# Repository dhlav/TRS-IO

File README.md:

# TRS-IO

TRS-IO gives a TRS-80 Model 1/III online capabilities and provides
access to a variety of services. TRS-IO currently features the
following capabilities:

1. Access to the <a href="https://retrostore.org">RetroStore</a>
2. <a href="http://frehd.com">FreHD</a> emulation
3. Access to files mounted on a SMB share or located on a micro-SD card
4. Access to remote servers via TCP
5. Virtual printer support

The TRS-IO versions for the Model 1 have some additional features that
are explained below. The following sections give an overview of TRS-IO as well as setup
instructions. This Github repository contains the complete source code
as well as the KiCad schematics for the PCB (Printed Circuit Board).
For the following descriptions it is assumed that an assembled TRS-IO
card is available.

### Overview

The figure below depicts the overall architecture. The TRS-80 machine
is connected to TRS-IO via the I/O Bus.  TRS-IO has a WiFi module that
connects to the local WiFi router. This allows TRS-IO to connect to
the Internet and access various services. Note that TRS-IO can only
connect to a 2.4 GHz WiFi network.

### Prerequisites

TRS-IO requires a TRS-80 Model III with 48kB of RAM or a Model 1 with 16kB of RAM.
Floppy disk drives or a cassette tape are not required.

### Feature list

TRS-IO support
TRS-IO comes in three different versions:

* TRS-IO for the Model III
* TRS-IO for the Model I using a builtin 32kB SRAM
* TRS-IO for the Model I using an FPGA

In the following, each of the versions is explained in detail.

### TRS-IO for the Model III

The following figure shows the top view of the TRS-IO card for the Model III:

1. Power supply via a micro-USB connector
2. Multi-color status LED
3. Status button
4. TRS-80 I/O bus connector
5. Micro-SD card reader
6. Disable FreHD jumper

The TRS-IO card needs to be connected to the TRS-80 Model III's I/O
Bus via a 50-pin ribbon cable (4). Furthermore, the TRS-IO card needs
a separate power supply via a standard 5V USB charger. The micro-USB
connector (1) plugs into the side of the TRS-IO card. The push button
(3) and the multi-color status LED (2) will be explained in the
configuration section.

### TRS-IO for the Model 1 (SRAM edition)

The following figure shows the top view of the TRS-IO card for the Model 1:

1. Power supply via a micro-USB connector
2. Multi-color status LED
3. Status button
4. TRS-80 I/O bus connector
5. Micro-SD card reader

The TRS-IO version for the Model 1 is almost identical to the Model III.
One difference is the I/O bus connector (4) is compatible with the 40-pin
expansion interface of the Model 1. There are several additional features
for the Model 1 version that are not relevant to the Model III version:

* A 32kB SRAM chip for a total of 48kB of total RAM.
* 25ms heartbeat timer to trigger the realtime clock.
* FreHD auto-boot for an unmodified M1.

### TRS-IO for the Model 1 (FPGA edition)

The TRS-IO project features a second version for the Model 1 that makes use
of an FGPA (Field Programmable Gate Array). Using an FPGA allows for some
advanced features not possible with the SRAM edition of TRS-IO. The following
figure shows the top view of the FPGA version for the Model 1:

1. Power supply via a micro-USB connector
2. Multi-color status LED
3. Status button
4. TRS-80 I/O bus connector
5. Micro-SD card reader
6. N/A
7. VGA connector
8. A15/VU configuration jumpers

This version of TRS-IO offers all the features of the SRAM edition of TRS-IO
as outlined in the previous section. Additionally, the FPGA edition also
offers a VGA connector (7) that can be used instead of a CRT monitor. This version
of TRS-IO also emlates the LE18 graphics cards. The color of the VGA signal can
be set to white (X=0), green (X=1), and amber (X=2) via the following OUT statements:

```OUT 31,0:OUT 31,5:OUT 31,X```

There are two configuation jumpers (8):
With the VU jumper, the ESP also powers the FPGA. When using this jumper, the FPGA
SHOULD NOT be powered via its own micro-USB connector; power should only be supplied
to the ESP's micro-USB connector (1). The A15 jumper regulates
the address range the FPGA responds to. Without the A15 jumper, the FPGA only
responds to memory read/write requests for the upper 32 kB (essentially mimicking the
upper RAM of the SRAM edition). With the A15 jumper, the FPGA will respond to the
complete 64kB address space of the Z80. This requires a modified Model 1 as the FPGA also
responds to ROM read requests.

### Configuring TRS-IO

The core of the TRS-IO card is an ESP32 microcontroller that features
a WiFi module that is used to connect to a WiFi router. After
physically connecting the TRS-IO card to a TRS-80 Model 1/III as
explained in the previous sections, the WiFi module on the ESP32
microcontroller first needs to be be configured with the credentials
of the local WiFi network.

While in setup mode, the TRS-IO's status LED will continuously blink
in white to indicate that it has not yet been configured. While in
that mode, TRS-IO will create an open access point called
"TRS-IO". Use a laptop to connect to this WiFi network and then use a
browser to visit URL <a
href="http://trs-io.local">trs-io.local</a>. The following web page
should appear in the browser:

Some hosts do not correctly handle mDNS that is used to resolve <a
href="http://trs-io.local">trs-io.local</a>. In that case, visit the
IP address <a href="http://192.168.4.1">192.168.4.1</a> instead.
The web interface shown above can be used to configure SSID and password of the WiFi
network that TRS-IO should connect to, the local timezone as well as
the credentials of a SMB share. For open networks leave the WiFi
password field empty. Note that TRS-IO cannot connect to WiFi networks
that use a capture portal. The timezone as well as the SMB share are
not required but will result in limited functionality.

Once all the information is provided, click on submit to upload the
parameters. TRS-IO will automatically reboot and try to connect to the
specified WiFi network. If successful, the LED will turn green for a
few seconds. If the credentials are wrong or if the specified WiFi
network is not accessible, the LED light will turn permanently red.

Note that TRS-IO will store all parameters in its local flash memory,
so the setup only needs to be performed once. Once TRS-IO is connected
to a WiFi router, it should still be possible to access URL <a
href="http://trs-io.local">trs-io.local</a> from a browser on the same
WiFi network. If mDNS is not supported by the host, the following BASIC
program can be used to determine TRS-IO's local IP address that was
assigned by the router:

```
10 OUT 236,16
20 OUT31,0:OUT31,4
30 C=INP(31):IF C=0 THEN END
40 PRINT CHR$(C);
50 GOTO 30
```

The web interface will also display two icons to indicate the status
of the SMB share and the micro-SD card (see screenshot above). Green
icons indicate that TRS-IO has access. Red icons indicate an error.
In that case, hovering the mouse over the red icon will display the
error message. It should be noted that TRS-IO needs to be rebooted
whenever a micro-SD card is inserted or ejected.

Pushing the status button will make the LED flash twice. The first time for
the WiFi status (green: WiFi connected; red: WiFi not connected) and a
second time for the SMB status (green: connected to SMB share; red:
not connected to SMB share). With proper configuration parameters, the
LED should flash green twice. Holding down the push button for more
than three seconds will erase all configuration parameters and place
TRS-IO back into setup mode (status LED flashing white). This
might be necessary if TRS-IO is moved to a different WiFi network.

The status LED indicates the state of TRS-IO:

* Blinking white: TRS-IO is not configured. It will create an open WiFi access point named "TRS-IO"
* Solid green: when TRS-IO has been configured with WiFi credentials and TRS-IO was able
  to connect to the WiFi network, the status LED will light in solid green for several seconds.
* Solid red: TRS-IO was configured with WiFi credentials but it was not possible to connect to the specified
  network. The reason could be wrong credentials or the specified network is itself offline. The push button can be
  used to reset TRS-IO into setup mode in case different credentials need to be provided.
* Solid blue: TRS-IO performs an OTA (Over-the-Air) update. TRS-IO will automatically detect
  newer firmware versions and will download and install the new firmware. The status LED will light solid blue during
  this process.
* Off: the status LED will be off during regular operations when TRS-IO is connected to the specified
  WiFi network and ready to accept commands from the TRS-80 Model III.
 
### FreHD

TRS-IO is compatible with the popular <a
href="http://frehd.com">FreHD</a> hard disk emulator. The FreHD disk
images can either be stored on a SMB share or on a micro-SD card.
If a micro-SD card is inserted, it will take precedence over
a mounted SMB share. Once TRS-IO is configured to access a SMB share,
simply copy the required files such as <a
href="http://members.iinet.net.au/~ianmav/trs80/downloads.htm">FREHD.ROM</a>
to the SMB share. Alternatively, the disk images can be transferred
to the micro-SD card. The IMPORT/EXPORT utilities will access files on the
SMB share or micro-SD card respectively.

### Virtual Printer Interface

TRS-IO support a virtual printer interface. Visiting <a
href="http://trs-io.local/printer">trs-io.local/printer</a> from a browser
will open the printer interface. Any printer output from the M1/MIII will
be displayed in the printer interface. If the host cannot resolve the mDNS name
trs-io.local, the above BASIC program can be used to determine the TRS-80's
IP address.

 ### Launching the native RetroStore Client

The <a href="https://retrostore.org">RetroStore</a> hosts applications
for the Tandy Radio Shack vintage computers and allows to seamlessly
download and run these applications without the need of cassettes or
floppy disks. TRS-IO acts as a gateway to the <a
href="https://retrostore.org">RetroStore</a>. This requires to run a
program on the TRS-80 that interfaces with TRS-IO. This program is
available as a regular <a
href="https://github.com/apuder/TRS-IO/blob/master/src/esp/components/retrostore/rsclient.cmd">CMD</a>
executable.  For TRS-80 machines with attached physical floppy disks,
this CMD executable can be copied to a floppy disk and launched the
usual way. For TRS-80 machines that have neither floppy disk drives
nor cassette drives, it is also possible to bootstrap the native
client via the following short BASIC program:
 
 ```BASIC
 10 OUT236,16
 20 OUT31,3
 30 OUT31,1
 40 N=INP(31)+256*INP(31)
 50 FOR X=1 TO N:POKE20735+X,INP(31):NEXT
 RUN
 SYSTEM
 *? /20736
 ```
 
The above BASIC program will download the CMD executable from TRS-IO
and launch the native client.  Note that this procedure needs to be
repeated every time the TRS-80 is turned on.
 
### Using the native RetroStore Client

After successfully launching the native RetroStore client, the monitor
of the TRS-80 should look like this:

The screenshot above shows the main menu of the native RetroStore
client. The arrow indicates the currently selected menu item.  The up
and down cursor keys can be used to move between the various menu
items. Hitting the ENTER key will activate the currently selected
menu item. Pressing CLEAR or BREAK in sub-menus will return to the
previous menu.
 
Keyboard controls:
 
 * Cursor up/down: toggle menu selection
 * ENTER: select current menu selection
 * BREAK/CLEAR: exit to previous screen

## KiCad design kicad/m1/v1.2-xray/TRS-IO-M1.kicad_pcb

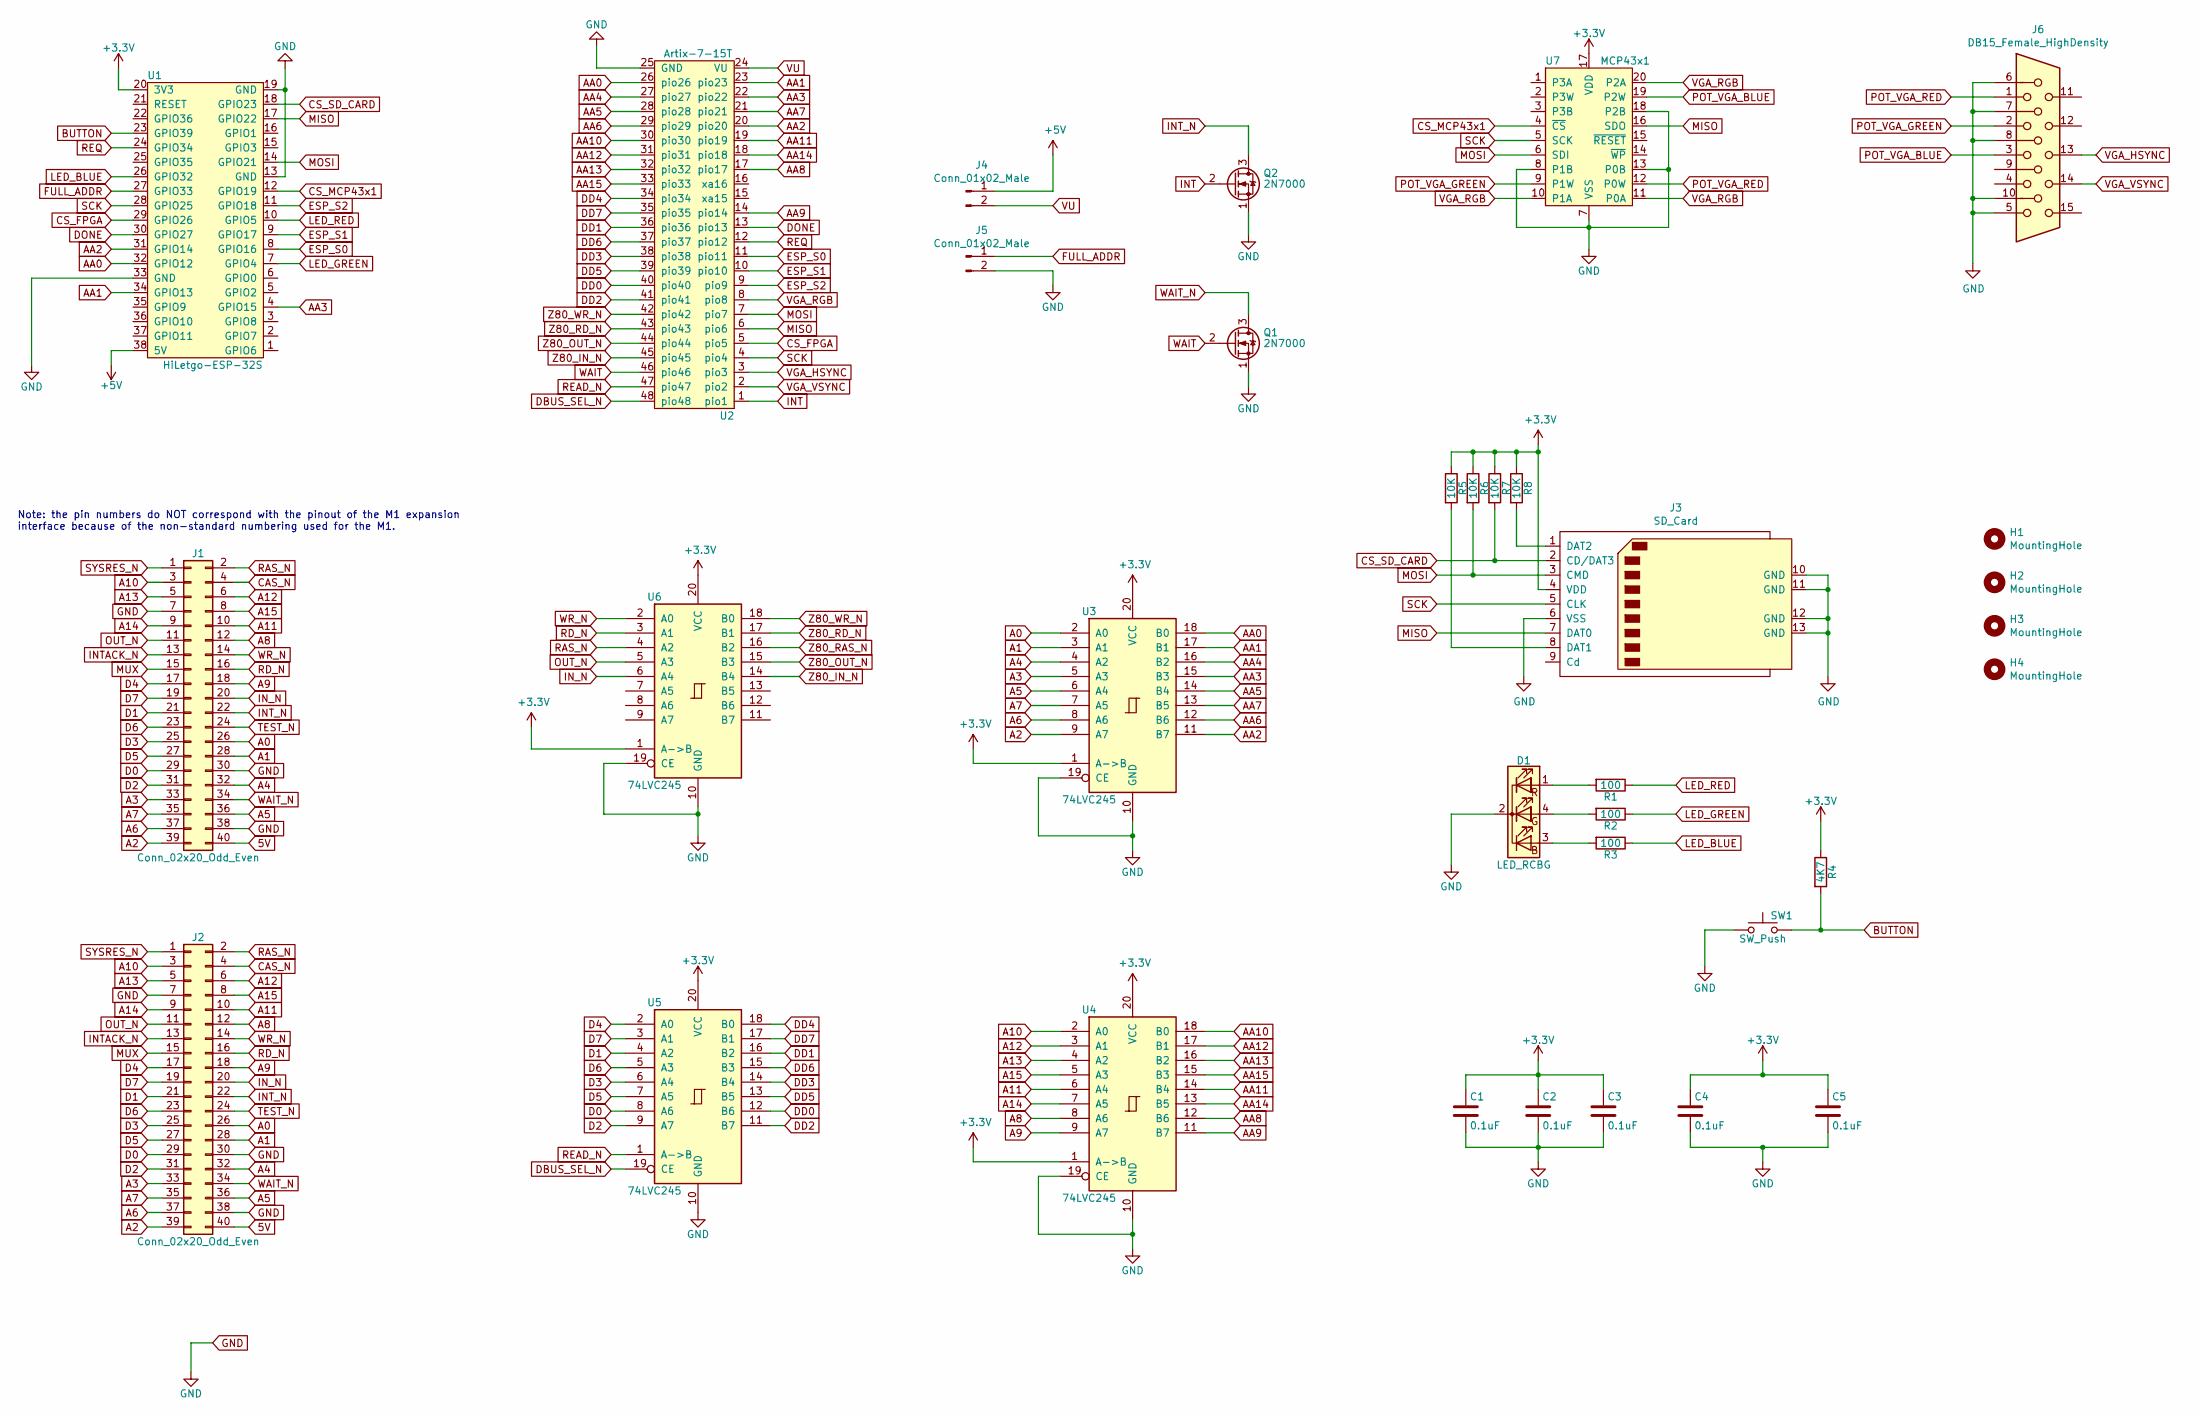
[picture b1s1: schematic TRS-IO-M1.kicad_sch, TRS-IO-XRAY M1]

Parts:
C1, C2, C3, C4, C5: 0.1uF; C_Disc_D3.0mm_W2.0mm_P2.50mm
D1: LED_RCBG; LED_D5.0mm-4_RGB
H1, H2, H3, H4: MountingHole; MountingHole_3mm_Pad_Via
J1: Conn_02x20_Odd_Even; PinHeader_2x20_P2.54mm_Vertical
J2: Conn_02x20_Odd_Even; TRSEDGE
J3: SD_Card; TFP09-2-12B
J4, J5: Conn_01x02_Male; PinHeader_1x02_P2.54mm_Vertical
J6: DB15_Female_HighDensity; DB_15F-VGA
Q1, Q2: 2N7000; TO-92_Inline
R1, R2, R3: 100; R_Axial_DIN0207_L6.3mm_D2.5mm_P7.62mm_Horizontal
R4: 4K7; R_Axial_DIN0207_L6.3mm_D2.5mm_P7.62mm_Horizontal
R5, R6, R7, R8: 10K; R_Axial_DIN0207_L6.3mm_D2.5mm_P7.62mm_Horizontal
SW1: SW_Push; SW_PUSH_6mm_H9.5mm
U1: HiLetgo-ESP-32S; DIP-38_W22.9mm
U2: Artix-7-15T; DIP-48_600_ELL
U3, U4, U5, U6: 74LVC245; DIP-20_W7.62mm
U7: MCP43x1; TSSOP-20_4.4x6.5mm_P0.65mm

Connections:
5V: J1.40, J2.40
+3V3: C1.1, C2.1, C3.1, C4.1, C5.1, J3.4 (VDD), R4.1, R5.1, R6.1, R7.1, R8.1, U1.20 (3V3), U3.1 (A->B), U3.20 (VCC), U4.1 (A->B), U4.20 (VCC), U5.20 (VCC), U6.1 (A->B), U6.20 (VCC), U7.17 (VDD)
+5V: J4.1, U1.38 (5V)
A0: J1.26, J2.26, U3.2 (A0)
A1: J1.28, J2.28, U3.3 (A1)
A2: J1.39, J2.39, U3.9 (A7)
A3: J1.33, J2.33, U3.5 (A3)
A4: J1.32, J2.32, U3.4 (A2)
A5: J1.36, J2.36, U3.6 (A4)
A6: J1.37, J2.37, U3.8 (A6)
A7: J1.35, J2.35, U3.7 (A5)
A8: J1.12, J2.12, U4.8 (A6)
A9: J1.18, J2.18, U4.9 (A7)
A10: J1.3, J2.3, U4.2 (A0)
A11: J1.10, J2.10, U4.6 (A4)
A12: J1.6, J2.6, U4.3 (A1)
A13: J1.5, J2.5, U4.4 (A2)
A14: J1.9, J2.9, U4.7 (A5)
A15: J1.8, J2.8, U4.5 (A3)
AA0: U1.32 (GPIO12), U2.26 (pio26), U3.18 (B0)
AA1: U1.34 (GPIO13), U2.23 (pio23), U3.17 (B1)
AA2: U1.31 (GPIO14), U2.20 (pio20), U3.11 (B7)
AA3: U1.4 (GPIO15), U2.22 (pio22), U3.15 (B3)
AA4: U2.27 (pio27), U3.16 (B2)
AA5: U2.28 (pio28), U3.14 (B4)
AA6: U2.29 (pio29), U3.12 (B6)
AA7: U2.21 (pio21), U3.13 (B5)
AA8: U2.17 (pio17), U4.12 (B6)
AA9: U2.14 (pio14), U4.11 (B7)
AA10: U2.30 (pio30), U4.18 (B0)
AA11: U2.19 (pio19), U4.14 (B4)
AA12: U2.31 (pio31), U4.17 (B1)
AA13: U2.32 (pio32), U4.16 (B2)
AA14: U2.18 (pio18), U4.13 (B5)
AA15: U2.33 (pio33), U4.15 (B3)
BUTTON: R4.2, SW1.2, U1.23 (GPIO39)
CAS_N: J1.4, J2.4
CS_FPGA: U1.29 (GPIO26), U2.5 (pio5)
CS_MCP43x1: U1.12 (GPIO19), U7.4 (~CS)
CS_SD_CARD: J3.2 (CD/DAT3), R7.2, U1.18 (GPIO23)
D0: J1.29, J2.29, U5.8 (A6)
D1: J1.21, J2.21, U5.4 (A2)
D2: J1.31, J2.31, U5.9 (A7)
D3: J1.25, J2.25, U5.6 (A4)
D4: J1.17, J2.17, U5.2 (A0)
D5: J1.27, J2.27, U5.7 (A5)
D6: J1.23, J2.23, U5.5 (A3)
D7: J1.19, J2.19, U5.3 (A1)
DBUS_SEL_N: U2.48 (pio48), U5.19 (CE)
DD0: U2.40 (pio40), U5.12 (B6)
DD1: U2.36 (pio36), U5.16 (B2)
DD2: U2.41 (pio41), U5.11 (B7)
DD3: U2.38 (pio38), U5.14 (B4)
DD4: U2.34 (pio34), U5.18 (B0)
DD5: U2.39 (pio39), U5.13 (B5)
DD6: U2.37 (pio37), U5.15 (B3)
DD7: U2.35 (pio35), U5.17 (B1)
DONE: U1.30 (GPIO27), U2.13 (pio13)
ESP_S0: U1.8 (GPIO16), U2.11 (pio11)
ESP_S1: U1.9 (GPIO17), U2.10 (pio10)
ESP_S2: U1.11 (GPIO18), U2.9 (pio9)
FULL_ADDR: J5.1, U1.27 (GPIO33)
GND: C1.2, C2.2, C3.2, C4.2, C5.2, D1.2 (K), J1.7, J1.30, J1.38, J2.7, J2.30, J2.38, J3.6 (VSS), J3.10 (GND), J3.11 (GND), J3.12 (GND), J3.13 (GND), J5.2, J6.5, J6.6, J6.7, J6.8, J6.10, Q1.1 (S), Q2.1 (S), SW1.1, U1.13 (GND), U1.19 (GND), U1.33 (GND), U2.25 (GND), U3.10 (GND), U3.19 (CE), U4.10 (GND), U4.19 (CE), U5.10 (GND), U6.10 (GND), U6.19 (CE), U7.7 (VSS), U7.8 (P1B), U7.13 (P0B), U7.18 (P2B)
INT: Q2.2 (G), U2.1 (pio1)
INTACK_N: J1.13, J2.13
INT_N: J1.22, J2.22, Q2.3 (D)
IN_N: J1.20, J2.20, U6.6 (A4)
LED_BLUE: R3.1, U1.26 (GPIO32)
LED_GREEN: R2.1, U1.7 (GPIO4)
LED_RED: R1.1, U1.10 (GPIO5)
MISO: J3.7 (DAT0), U1.17 (GPIO22), U2.6 (pio6), U7.16 (SDO)
MOSI: J3.3 (CMD), R6.2, U1.14 (GPIO21), U2.7 (pio7), U7.6 (SDI)
MUX: J1.15, J2.15
unnamed: D1.1 (RA), R1.2
unnamed: D1.3 (BA), R3.2
unnamed: D1.4 (GA), R2.2
unnamed: J3.1 (DAT2), R8.2
unnamed: J3.8 (DAT1), R5.2
OUT_N: J1.11, J2.11, U6.5 (A3)
POT_VGA_BLUE: J6.3, U7.19 (P2W)
POT_VGA_GREEN: J6.2, U7.9 (P1W)
POT_VGA_RED: J6.1, U7.12 (P0W)
RAS_N: J1.2, J2.2, U6.4 (A2)
RD_N: J1.16, J2.16, U6.3 (A1)
READ_N: U2.47 (pio47), U5.1 (A->B)
REQ: U1.24 (GPIO34), U2.12 (pio12)
SCK: J3.5 (CLK), U1.28 (GPIO25), U2.4 (pio4), U7.5 (SCK)
SYSRES_N: J1.1, J2.1
TEST_N: J1.24, J2.24
VGA_HSYNC: J6.13, U2.3 (pio3)
VGA_RGB: U2.8 (pio8), U7.10 (P1A), U7.11 (P0A), U7.20 (P2A)
VGA_VSYNC: J6.14, U2.2 (pio2)
VU: J4.2, U2.24 (VU)
WAIT: Q1.2 (G), U2.46 (pio46)
WAIT_N: J1.34, J2.34, Q1.3 (D)
WR_N: J1.14, J2.14, U6.2 (A0)
Z80_IN_N: U2.45 (pio45), U6.14 (B4)
Z80_OUT_N: U2.44 (pio44), U6.15 (B3)
Z80_RAS_N: U6.16 (B2)
Z80_RD_N: U2.43 (pio43), U6.17 (B1)
Z80_WR_N: U2.42 (pio42), U6.18 (B0)

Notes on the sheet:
Note: the pin numbers do NOT correspond with the pinout of the M1 expansion interface because of the non-standard numbering used for the M1.

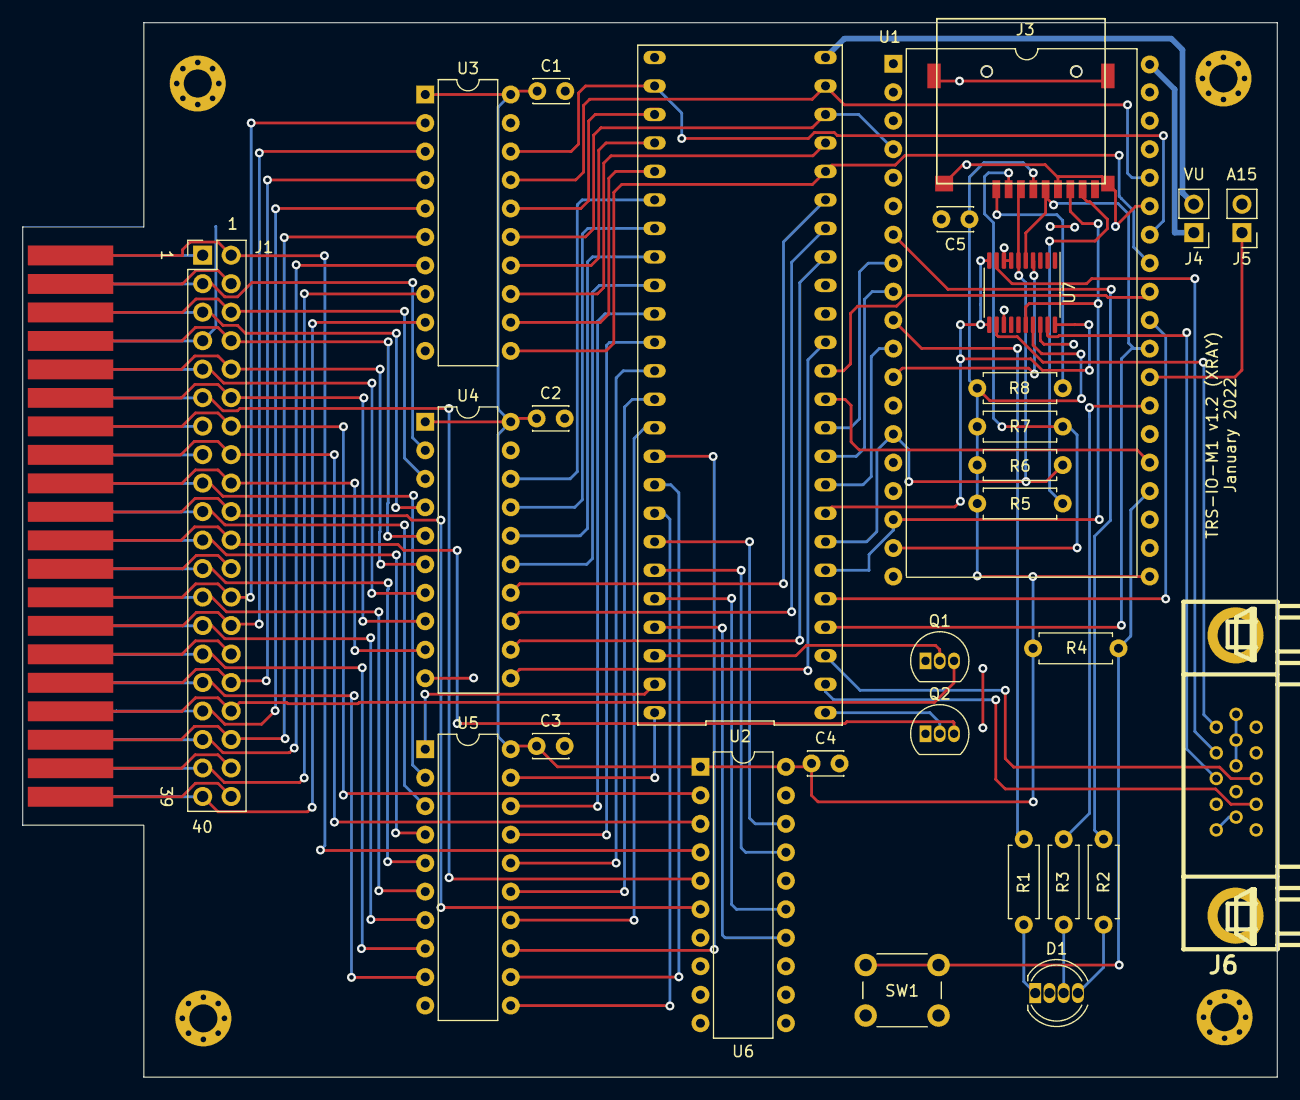
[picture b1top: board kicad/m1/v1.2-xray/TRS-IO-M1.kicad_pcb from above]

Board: 2 copper layers, 111.9 x 94.0 mm, 34 parts (0 on the bottom side), 100 nets.

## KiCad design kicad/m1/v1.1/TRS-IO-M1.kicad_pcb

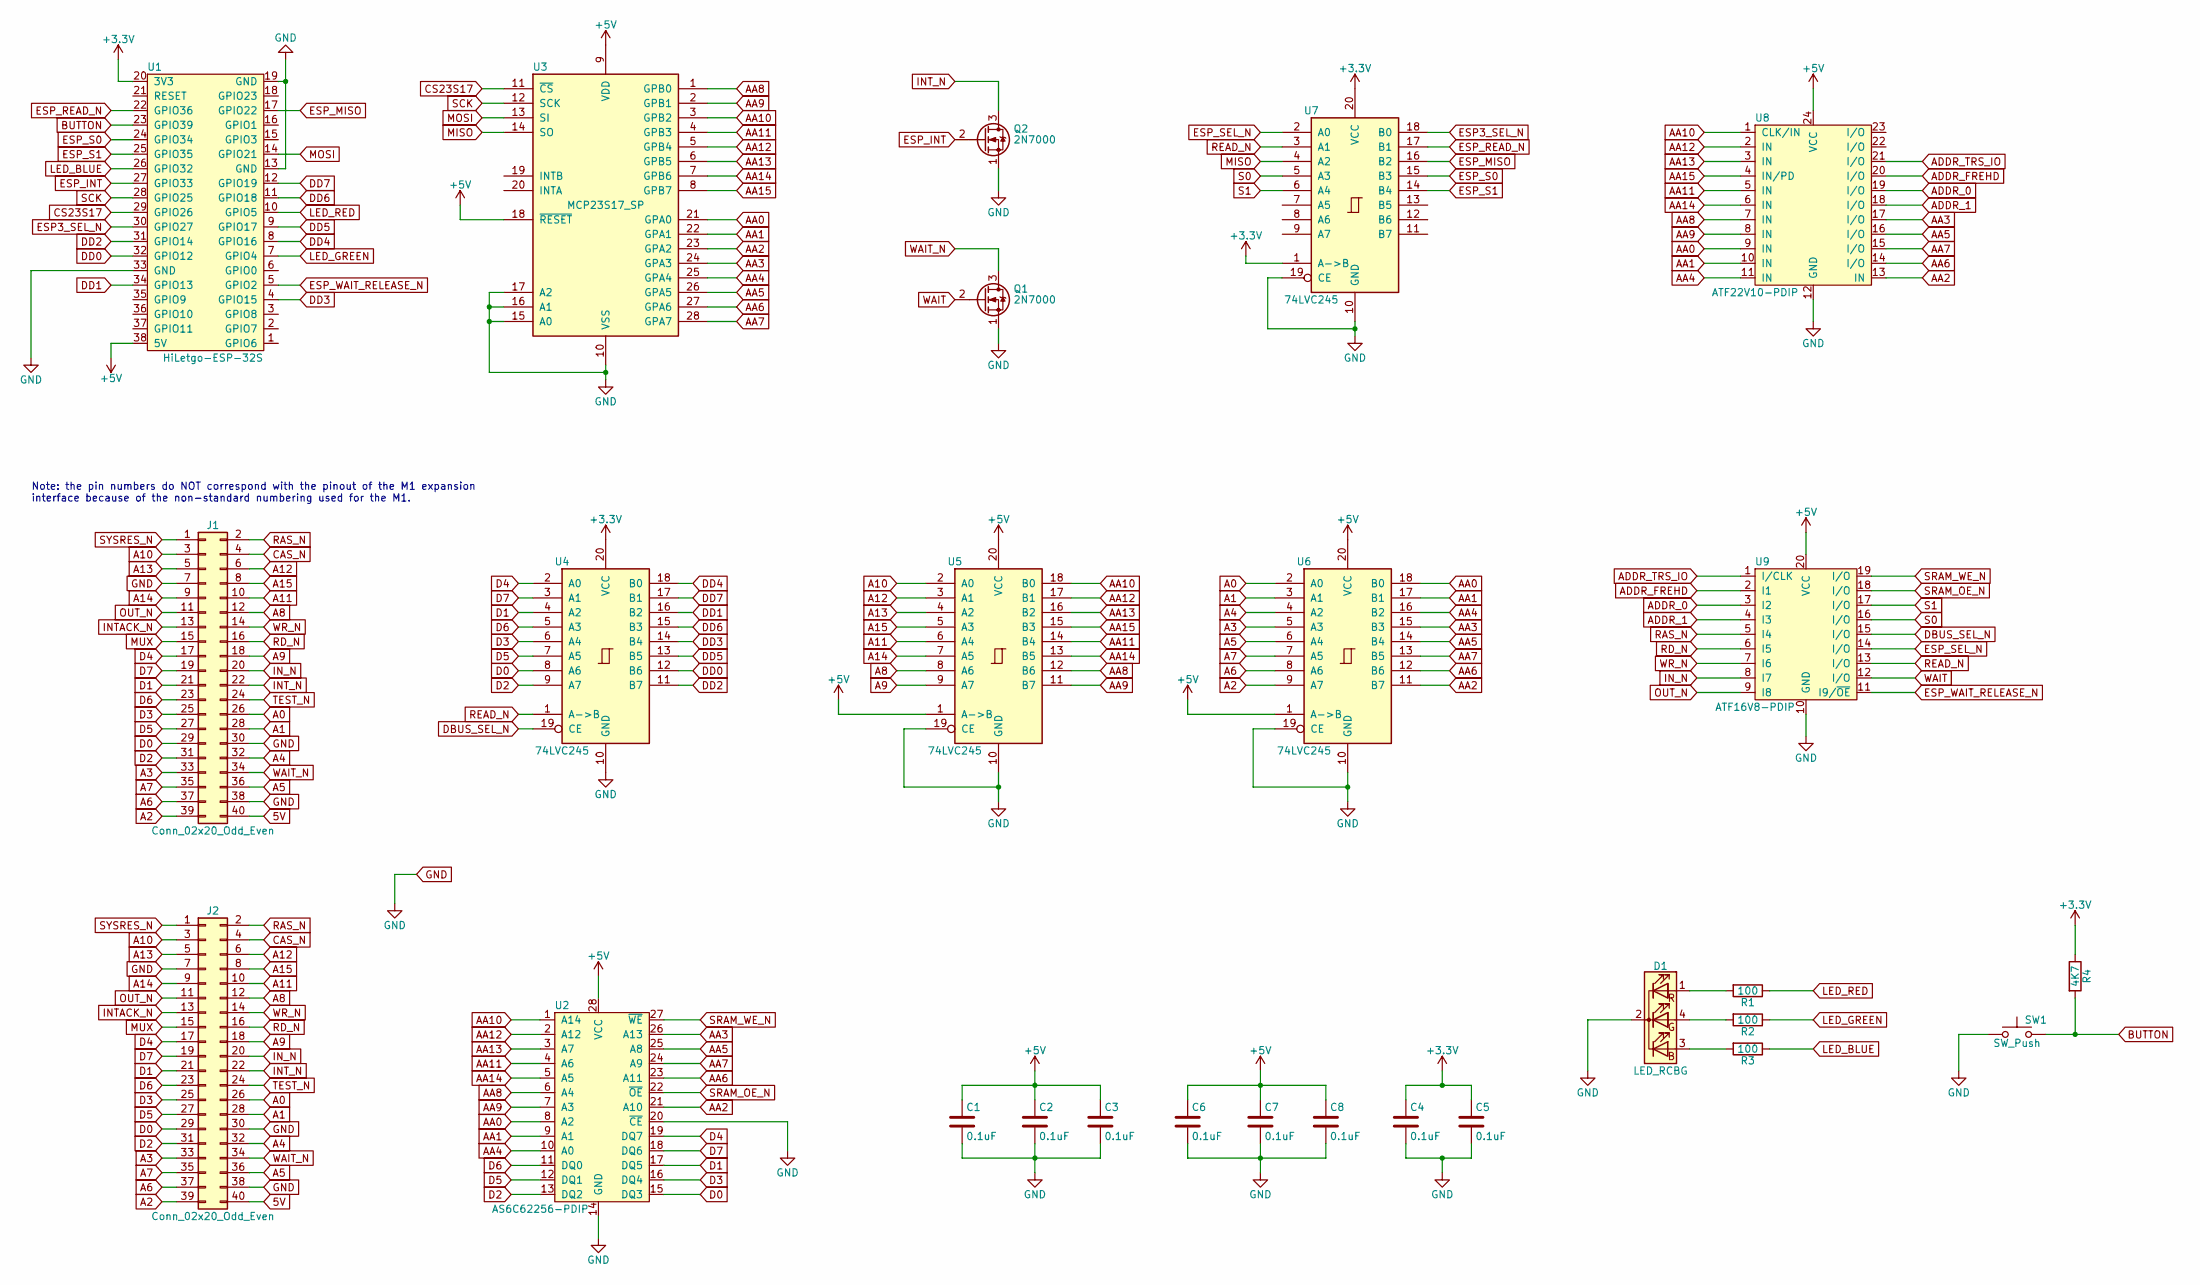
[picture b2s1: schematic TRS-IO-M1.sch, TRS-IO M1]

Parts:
C1, C2, C3, C4, C5, C6, C7, C8: 0.1uF; C_Disc_D3.0mm_W2.0mm_P2.50mm
D1: LED_RCBG; LED_D5.0mm-4_RGB
J1: Conn_02x20_Odd_Even; PinHeader_2x20_P2.54mm_Vertical
J2: Conn_02x20_Odd_Even; TRSEDGE
Q1, Q2: 2N7000; TO-92_Inline
R1, R2, R3: 100; R_Axial_DIN0207_L6.3mm_D2.5mm_P7.62mm_Horizontal
R4: 4K7; R_Axial_DIN0207_L6.3mm_D2.5mm_P7.62mm_Horizontal
SW1: SW_Push; SW_PUSH_6mm_H9.5mm
U1: HiLetgo-ESP-32S; DIP-38_W22.9mm
U2: AS6C62256-PDIP; DIP-28_W15.24mm
U3: MCP23S17_SP; DIP-28_W7.62mm
U4, U5, U6, U7: 74LVC245; DIP-20_W7.62mm
U8: ATF22V10-PDIP; DIP-24_W7.62mm
U9: ATF16V8-PDIP; DIP-20_W7.62mm

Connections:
5V: J1.40, J2.40
+3V3: C4.1, C5.1, R4.1, U1.20 (3V3), U4.20 (VCC), U7.1 (A->B), U7.20 (VCC)
+5V: C1.1, C2.1, C3.1, C6.1, C7.1, C8.1, U1.38 (5V), U2.28 (VCC), U3.9 (VDD), U3.18 (~RESET~), U5.1 (A->B), U5.20 (VCC), U6.1 (A->B), U6.20 (VCC), U8.24 (VCC), U9.20 (VCC)
A0: J1.26, J2.26, U6.2 (A0)
A1: J1.28, J2.28, U6.3 (A1)
A2: J1.39, J2.39, U6.9 (A7)
A3: J1.33, J2.33, U6.5 (A3)
A4: J1.32, J2.32, U6.4 (A2)
A5: J1.36, J2.36, U6.6 (A4)
A6: J1.37, J2.37, U6.8 (A6)
A7: J1.35, J2.35, U6.7 (A5)
A8: J1.12, J2.12, U5.8 (A6)
A9: J1.18, J2.18, U5.9 (A7)
A10: J1.3, J2.3, U5.2 (A0)
A11: J1.10, J2.10, U5.6 (A4)
A12: J1.6, J2.6, U5.3 (A1)
A13: J1.5, J2.5, U5.4 (A2)
A14: J1.9, J2.9, U5.7 (A5)
A15: J1.8, J2.8, U5.5 (A3)
AA0: U2.8 (A2), U3.21 (GPA0), U6.18 (B0), U8.9 (IN)
AA1: U2.9 (A1), U3.22 (GPA1), U6.17 (B1), U8.10 (IN)
AA2: U2.21 (A10), U3.23 (GPA2), U6.11 (B7), U8.13 (IN)
AA3: U2.26 (A13), U3.24 (GPA3), U6.15 (B3), U8.17 (I/O)
AA4: U2.10 (A0), U3.25 (GPA4), U6.16 (B2), U8.11 (IN)
AA5: U2.25 (A8), U3.26 (GPA5), U6.14 (B4), U8.16 (I/O)
AA6: U2.23 (A11), U3.27 (GPA6), U6.12 (B6), U8.14 (I/O)
AA7: U2.24 (A9), U3.28 (GPA7), U6.13 (B5), U8.15 (I/O)
AA8: U2.6 (A4), U3.1 (GPB0), U5.12 (B6), U8.7 (IN)
AA9: U2.7 (A3), U3.2 (GPB1), U5.11 (B7), U8.8 (IN)
AA10: U2.1 (A14), U3.3 (GPB2), U5.18 (B0), U8.1 (CLK/IN)
AA11: U2.4 (A6), U3.4 (GPB3), U5.14 (B4), U8.5 (IN)
AA12: U2.2 (A12), U3.5 (GPB4), U5.17 (B1), U8.2 (IN)
AA13: U2.3 (A7), U3.6 (GPB5), U5.16 (B2), U8.3 (IN)
AA14: U2.5 (A5), U3.7 (GPB6), U5.13 (B5), U8.6 (IN)
AA15: U3.8 (GPB7), U5.15 (B3), U8.4 (IN/PD)
ADDR_0: U8.19 (I/O), U9.3 (I2)
ADDR_1: U8.18 (I/O), U9.4 (I3)
ADDR_FREHD: U8.20 (I/O), U9.2 (I1)
ADDR_TRS_IO: U8.21 (I/O), U9.1 (I/CLK)
BUTTON: R4.2, SW1.2, U1.23 (GPIO39)
CAS_N: J1.4, J2.4
CS23S17: U1.29 (GPIO26), U3.11 (~CS~)
D0: J1.29, J2.29, U2.15 (DQ3), U4.8 (A6)
D1: J1.21, J2.21, U2.17 (DQ5), U4.4 (A2)
D2: J1.31, J2.31, U2.13 (DQ2), U4.9 (A7)
D3: J1.25, J2.25, U2.16 (DQ4), U4.6 (A4)
D4: J1.17, J2.17, U2.19 (DQ7), U4.2 (A0)
D5: J1.27, J2.27, U2.12 (DQ1), U4.7 (A5)
D6: J1.23, J2.23, U2.11 (DQ0), U4.5 (A3)
D7: J1.19, J2.19, U2.18 (DQ6), U4.3 (A1)
DBUS_SEL_N: U4.19 (CE), U9.15 (I/O)
DD0: U1.32 (GPIO12), U4.12 (B6)
DD1: U1.34 (GPIO13), U4.16 (B2)
DD2: U1.31 (GPIO14), U4.11 (B7)
DD3: U1.4 (GPIO15), U4.14 (B4)
DD4: U1.8 (GPIO16), U4.18 (B0)
DD5: U1.9 (GPIO17), U4.13 (B5)
DD6: U1.11 (GPIO18), U4.15 (B3)
DD7: U1.12 (GPIO19), U4.17 (B1)
ESP3_SEL_N: U1.30 (GPIO27), U7.18 (B0)
ESP_INT: Q2.2 (G), U1.27 (GPIO33)
ESP_MISO: U1.17 (GPIO22), U7.16 (B2)
ESP_READ_N: U1.22 (GPIO36), U7.17 (B1)
ESP_S0: U1.24 (GPIO34), U7.15 (B3)
ESP_S1: U1.25 (GPIO35), U7.14 (B4)
ESP_SEL_N: U7.2 (A0), U9.14 (I/O)
ESP_WAIT_RELEASE_N: U1.5 (GPIO2), U9.11 (I9/~OE)
GND: C1.2, C2.2, C3.2, C4.2, C5.2, C6.2, C7.2, C8.2, D1.2 (K), J1.7, J1.30, J1.38, J2.7, J2.30, J2.38, Q1.1 (S), Q2.1 (S), SW1.1, U1.13 (GND), U1.19 (GND), U1.33 (GND), U2.14 (GND), U2.20 (~CE), U3.10 (VSS), U3.15 (A0), U3.16 (A1), U3.17 (A2), U4.10 (GND), U5.10 (GND), U5.19 (CE), U6.10 (GND), U6.19 (CE), U7.10 (GND), U7.19 (CE), U8.12 (GND), U9.10 (GND)
INTACK_N: J1.13, J2.13
INT_N: J1.22, J2.22, Q2.3 (D)
IN_N: J1.20, J2.20, U9.8 (I7)
LED_BLUE: R3.1, U1.26 (GPIO32)
LED_GREEN: R2.1, U1.7 (GPIO4)
LED_RED: R1.1, U1.10 (GPIO5)
MISO: U3.14 (SO), U7.4 (A2)
MOSI: U1.14 (GPIO21), U3.13 (SI)
MUX: J1.15, J2.15
unnamed: D1.1 (RA), R1.2
unnamed: D1.3 (BA), R3.2
unnamed: D1.4 (GA), R2.2
OUT_N: J1.11, J2.11, U9.9 (I8)
RAS_N: J1.2, J2.2, U9.5 (I4)
RD_N: J1.16, J2.16, U9.6 (I5)
READ_N: U4.1 (A->B), U7.3 (A1), U9.13 (I/O)
S0: U7.5 (A3), U9.16 (I/O)
S1: U7.6 (A4), U9.17 (I/O)
SCK: U1.28 (GPIO25), U3.12 (SCK)
SRAM_OE_N: U2.22 (~OE), U9.18 (I/O)
SRAM_WE_N: U2.27 (~WE), U9.19 (I/O)
SYSRES_N: J1.1, J2.1
TEST_N: J1.24, J2.24
WAIT: Q1.2 (G), U9.12 (I/O)
WAIT_N: J1.34, J2.34, Q1.3 (D)
WR_N: J1.14, J2.14, U9.7 (I6)

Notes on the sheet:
Note: the pin numbers do NOT correspond with the pinout of the M1 expansion interface because of the non-standard numbering used for the M1.

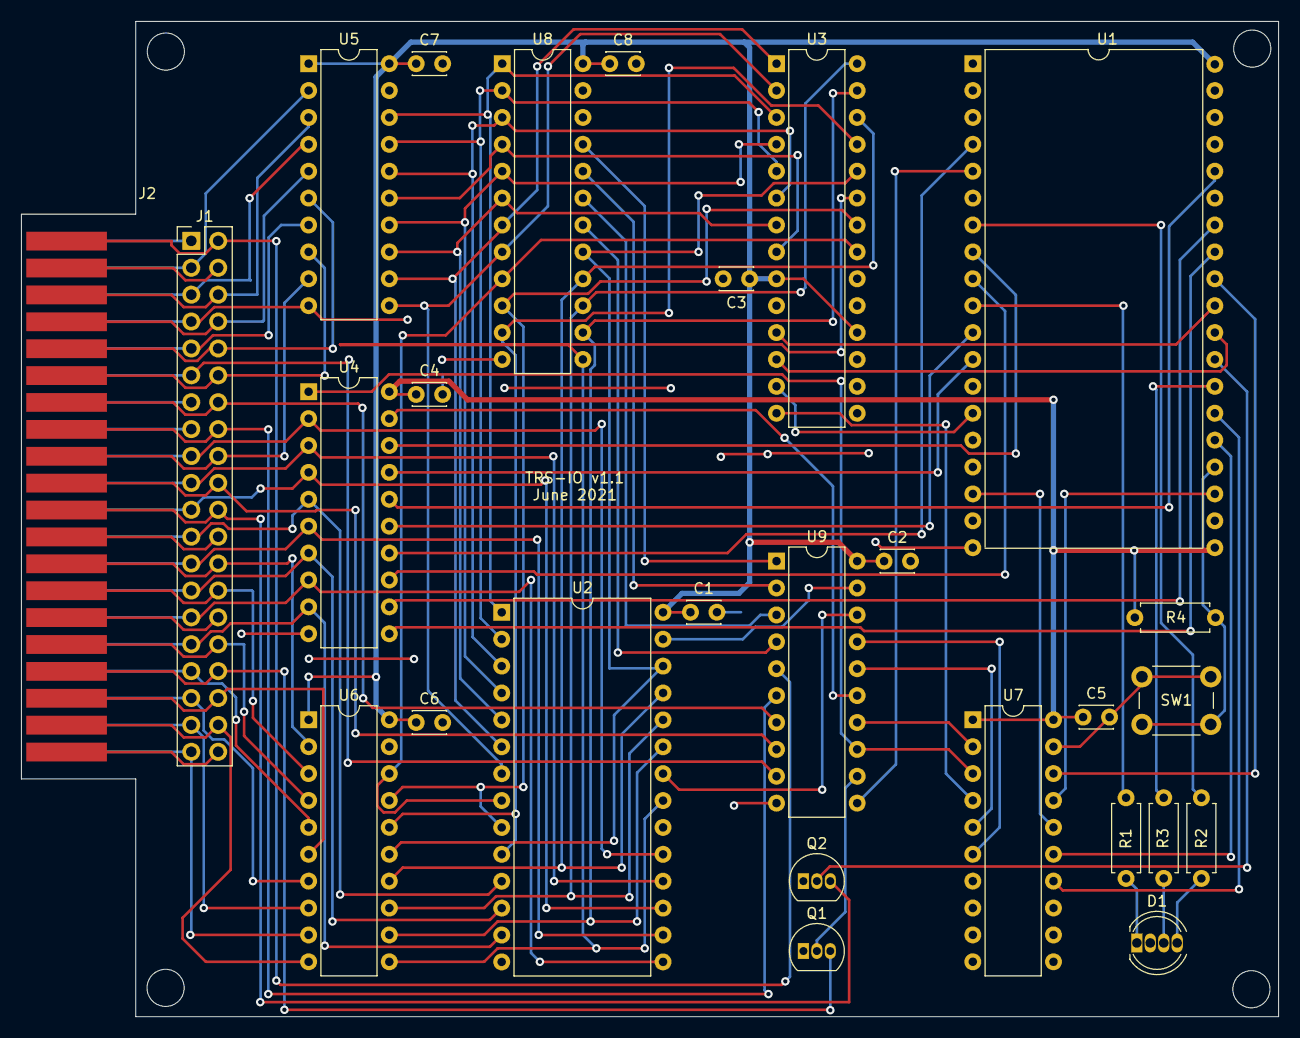
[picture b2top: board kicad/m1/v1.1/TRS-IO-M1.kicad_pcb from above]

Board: 2 copper layers, 118.7 x 94.0 mm, 27 parts (0 on the bottom side), 94 nets.

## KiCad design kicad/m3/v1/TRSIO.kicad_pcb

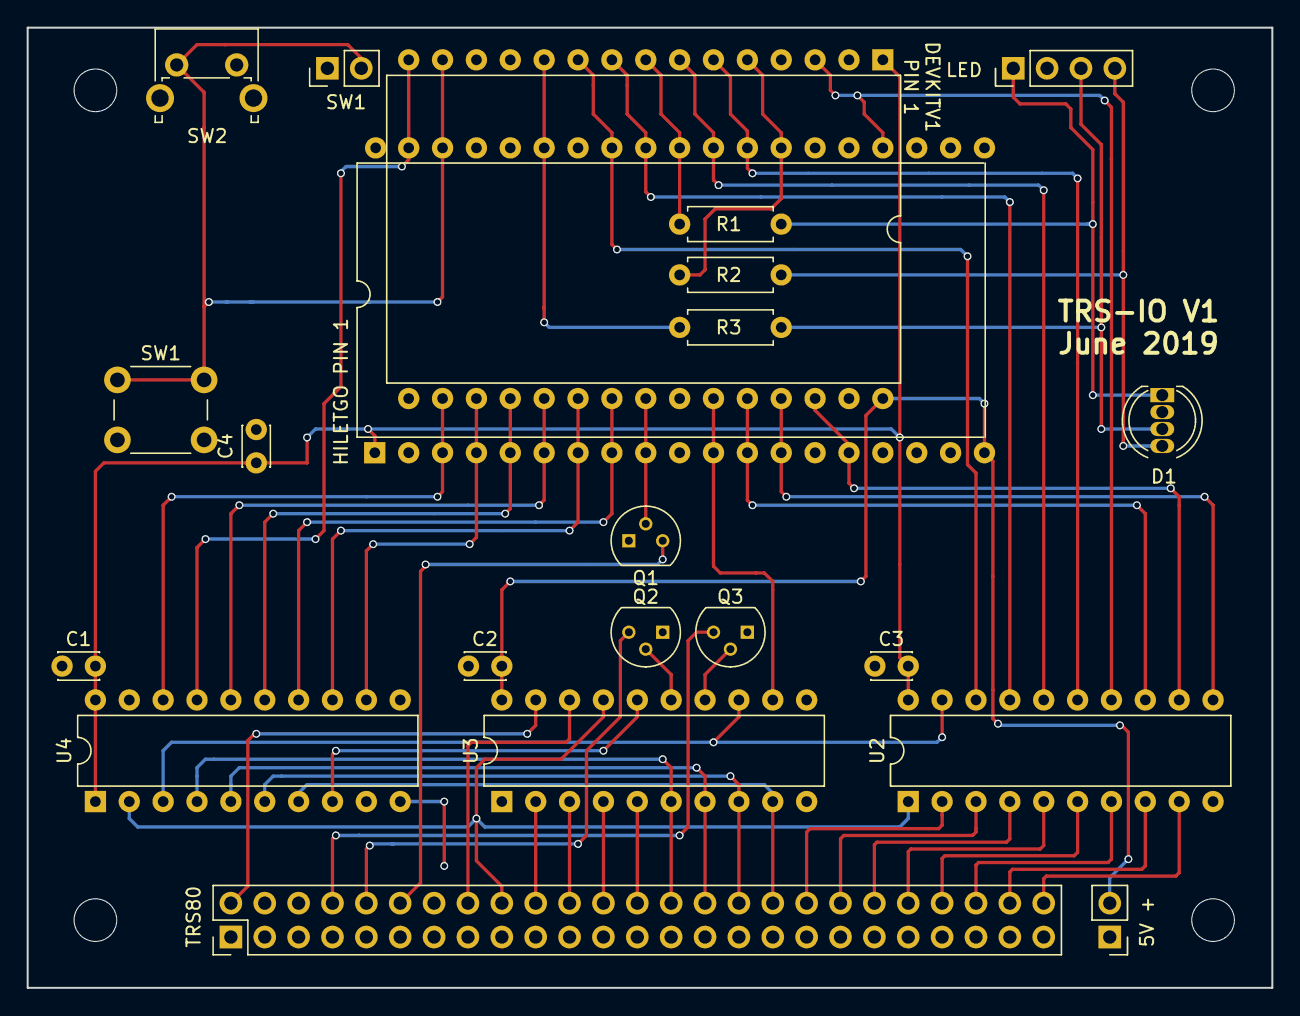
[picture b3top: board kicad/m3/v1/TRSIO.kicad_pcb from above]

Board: 2 copper layers, 93.3 x 72.0 mm, 22 parts (0 on the bottom side), 53 nets.

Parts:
C1, C2, C3, C4: 0.1; C_Disc_D3.0mm_W2.0mm_P2.50mm
D1: LED_RCBG; LED_D5.0mm-4
J1: TRS80; Pin_Header_Straight_2x25_Pitch2.54mm
J2: +5V; Pin_Header_Straight_1x02_Pitch2.54mm
J3: BUTTON; Pin_Header_Straight_1x02_Pitch2.54mm
J4: LED; Pin_Header_Straight_1x04_Pitch2.54mm
Q1, Q2, Q3: 2N7000; TO-92_Molded_Narrow
R1, R2, R3: 100; R_Axial_DIN0207_L6.3mm_D2.5mm_P7.62mm_Horizontal
SW1: SW_Push; SW_PUSH_6mm_h9.5mm
SW2: Right Angle; SW_Tactile_SPST_Angled_PTS645Vx31-2LFS
U1A1: ESP32S; DIP-38_W22.9mm
U1B1: ESP32_AliExpress; DIP-30_W25.4mm
U2, U4: 74LVC245; DIP-20_W7.62mm
U3: GAL16V8; DIP-20_W7.62mm

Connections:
+3V3: C1.1, C3.1, C4.1, U1A1.1, U1B1.1, U2.20, U4.1, U4.20
+5V: C2.1, J2.2, U1A1.19, U1B1.30, U3.20
//IORQ: J1.49, U3.19
//OUT: J1.35, U3.18
/A4: J1.25, U3.5
/A5: J1.27, U3.4
/A6: J1.29, U3.3
/A7: J1.31, U3.2
/D0: J1.1, U2.9
/D1: J1.3, U2.8
/D2: J1.5, U2.7
/D3: J1.7, U2.6
/D4: J1.9, U2.5
/D5: J1.11, U2.4
/D6: J1.13, U2.3
/D7: J1.15, U2.2
/ESP32_IN: U1A1.3, U1B1.17, U4.18
/ESP32_INT: Q1.2, U1A1.9, U1B1.23
/ESP32_P31: U1A1.4, U1B1.18, U4.12
/ESP32_SEL: U1A1.37, U1B1.15, U4.17
/ESP32_WAIT: U1A1.11, U1B1.25, U3.12
/ESP_EXTIOSEL: Q3.2, U3.14
/ESP_P31: U3.16, U4.8
/ESP_SEL: U2.19, U3.13, U4.3
/EXTIOSEL: J1.43, Q3.3
/IN: J1.33, U2.1, U3.17, U4.2
/IOINT: J1.39, Q1.3
/IOWAIT: J1.41, Q2.3
/WAIT: Q2.2, U3.15
A0: J1.17, U3.9, U4.7
A1: J1.19, U3.8, U4.6
A2: J1.21, U3.7, U4.5
A3: J1.23, U3.6, U4.4
BUTTON: J3.2, SW1.1, SW2.1, U1A1.36, U1B1.14
ESP32_A0: U1A1.7, U1B1.21, U4.13
ESP32_A1: U1A1.8, U1B1.22, U4.14
ESP32_A2: U1A1.5, U1B1.19, U4.15
ESP32_A3: U1A1.6, U1B1.20, U4.16
ESP32_D0: U1A1.13, U1B1.27, U2.11
ESP32_D1: U1A1.15, U1B1.28, U2.12
ESP32_D2: U1A1.12, U1B1.26, U2.13
ESP32_D3: U1A1.23, U1B1.3, U2.14
ESP32_D4: U1A1.27, U1B1.6, U2.15
ESP32_D5: U1A1.28, U1B1.7, U2.16
ESP32_D6: U1A1.30, U1B1.9, U2.17
ESP32_D7: U1A1.31, U1B1.10, U2.18
EXT_BLUE: D1.3, J4.3, R3.2
EXT_GREEN: D1.4, J4.4, R2.2
EXT_RED: D1.1, J4.1, R1.2
GND: C1.2, C2.2, C3.2, C4.2, D1.2, J1.2, J1.4, J1.6, J1.8, J1.10, J1.12, J1.14, J1.16, J1.18, J1.20, J1.22, J1.24, J1.26, J1.28, J1.30, J1.32, J1.34, J1.36, J1.38, J1.40, J1.42, J1.44, J1.46, J1.48, J1.50, J2.1, J3.1, J4.2, Q1.1, Q2.1, Q3.1, SW1.2, SW2.2, U1A1.14, U1A1.32, U1A1.38, U1B1.2, U1B1.29, U2.10, U3.10, U4.9, U4.10, U4.19
LED_BLUE: R3.1, U1A1.33, U1B1.11
LED_GREEN: R2.1, U1A1.26, U1B1.5
LED_RED: R1.1, U1A1.29, U1B1.8
